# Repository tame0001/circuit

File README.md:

# CircuitDesign
Repository to keep electronics circuit design

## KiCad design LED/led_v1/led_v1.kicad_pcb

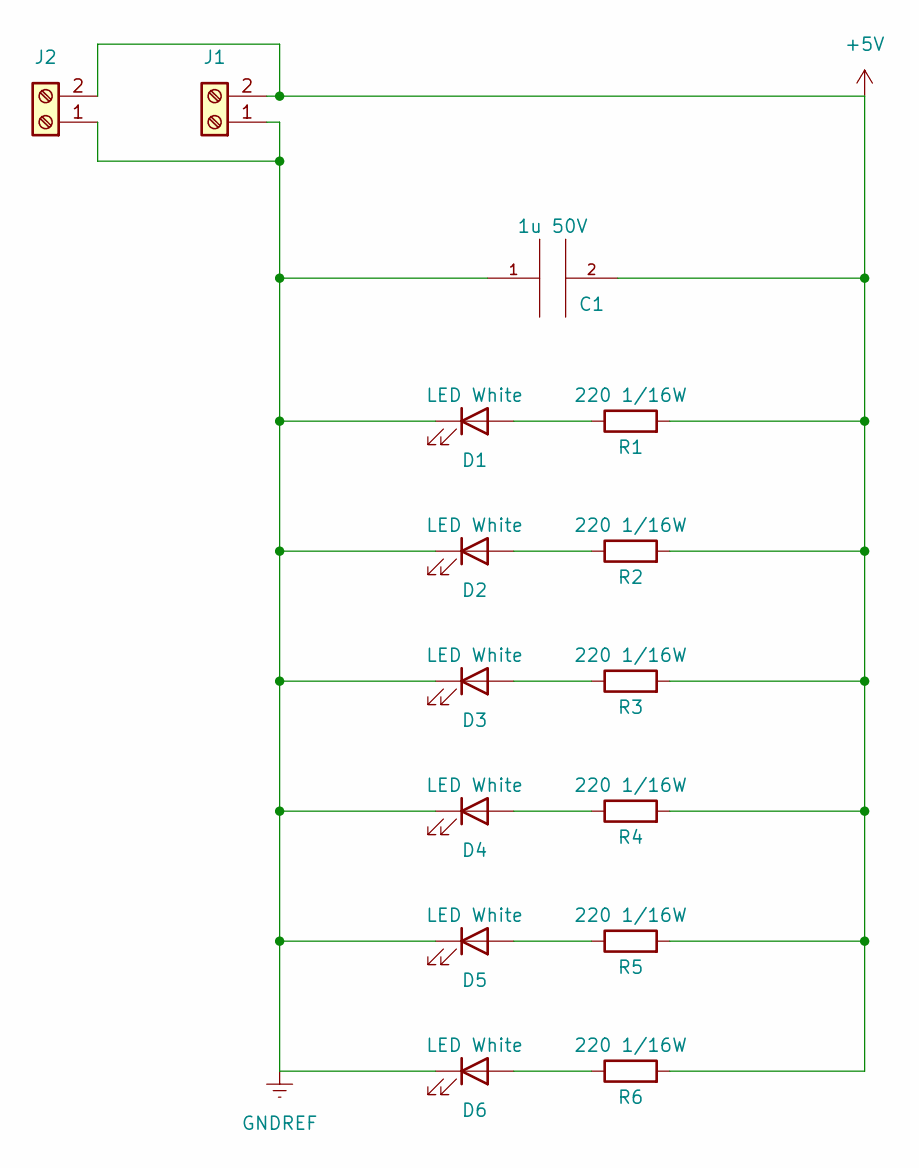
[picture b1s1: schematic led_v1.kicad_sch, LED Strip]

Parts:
C1: 1u 50V; C_0805_2012Metric; Part Number CL21B105KBFNNNE; JLC 0805
D1, D2, D3, D4, D5, D6: LED White; LED_0603_1608Metric; Part Number 19-217/T1D-CQ2R2TY/3T; JLC LED_0603
J1, J2: Screw_Terminal_01x02; TerminalBlock_Phoenix_MKDS-1,5-2-5.08_1x02_P5.08mm_Horizont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
R1, R2, R3, R4, R5, R6: 220 1/16W; R_0402_1005Metric; Part Number 0402WGF2200TCE; JLC 0402

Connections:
+5V: C1.2, J1.2, J2.2, R1.2, R2.2, R3.2, R4.2, R5.2, R6.2
GNDREF: C1.1, D1.1 (K), D2.1 (K), D3.1 (K), D4.1 (K), D5.1 (K), D6.1 (K), J1.1, J2.1
unnamed: D1.2 (A), R1.1
unnamed: D2.2 (A), R2.1
unnamed: D3.2 (A), R3.1
unnamed: D4.2 (A), R4.1
unnamed: D5.2 (A), R5.1
unnamed: D6.2 (A), R6.1

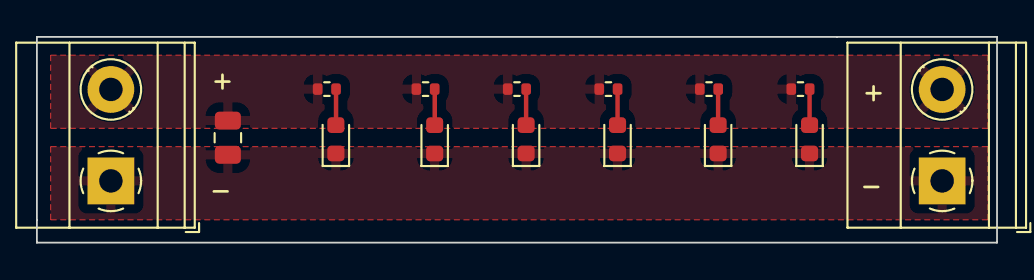
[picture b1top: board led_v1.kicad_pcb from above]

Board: 2 copper layers, 53.3 x 11.4 mm, 15 parts (0 on the bottom side), 8 nets.

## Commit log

2020-07-15 Add symbols and footprints
2021-01-02 Create template for Arduino project
2021-01-02 Add main processor
2021-01-04 Add 16 crystal
2021-01-06 add capacitors for crystal
2021-01-06 connect pin to MCU
2021-01-07 Add linear regulator
2021-01-08 Select n-mosfet for building relay
2022-02-24 Remove old files
2022-02-24 led version schematic
2022-02-28 Send order for v1
2022-03-20 update gitignore file
